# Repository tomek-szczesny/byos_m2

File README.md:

# byos_m2
Build Your Own System - a collection of stackable add-ons

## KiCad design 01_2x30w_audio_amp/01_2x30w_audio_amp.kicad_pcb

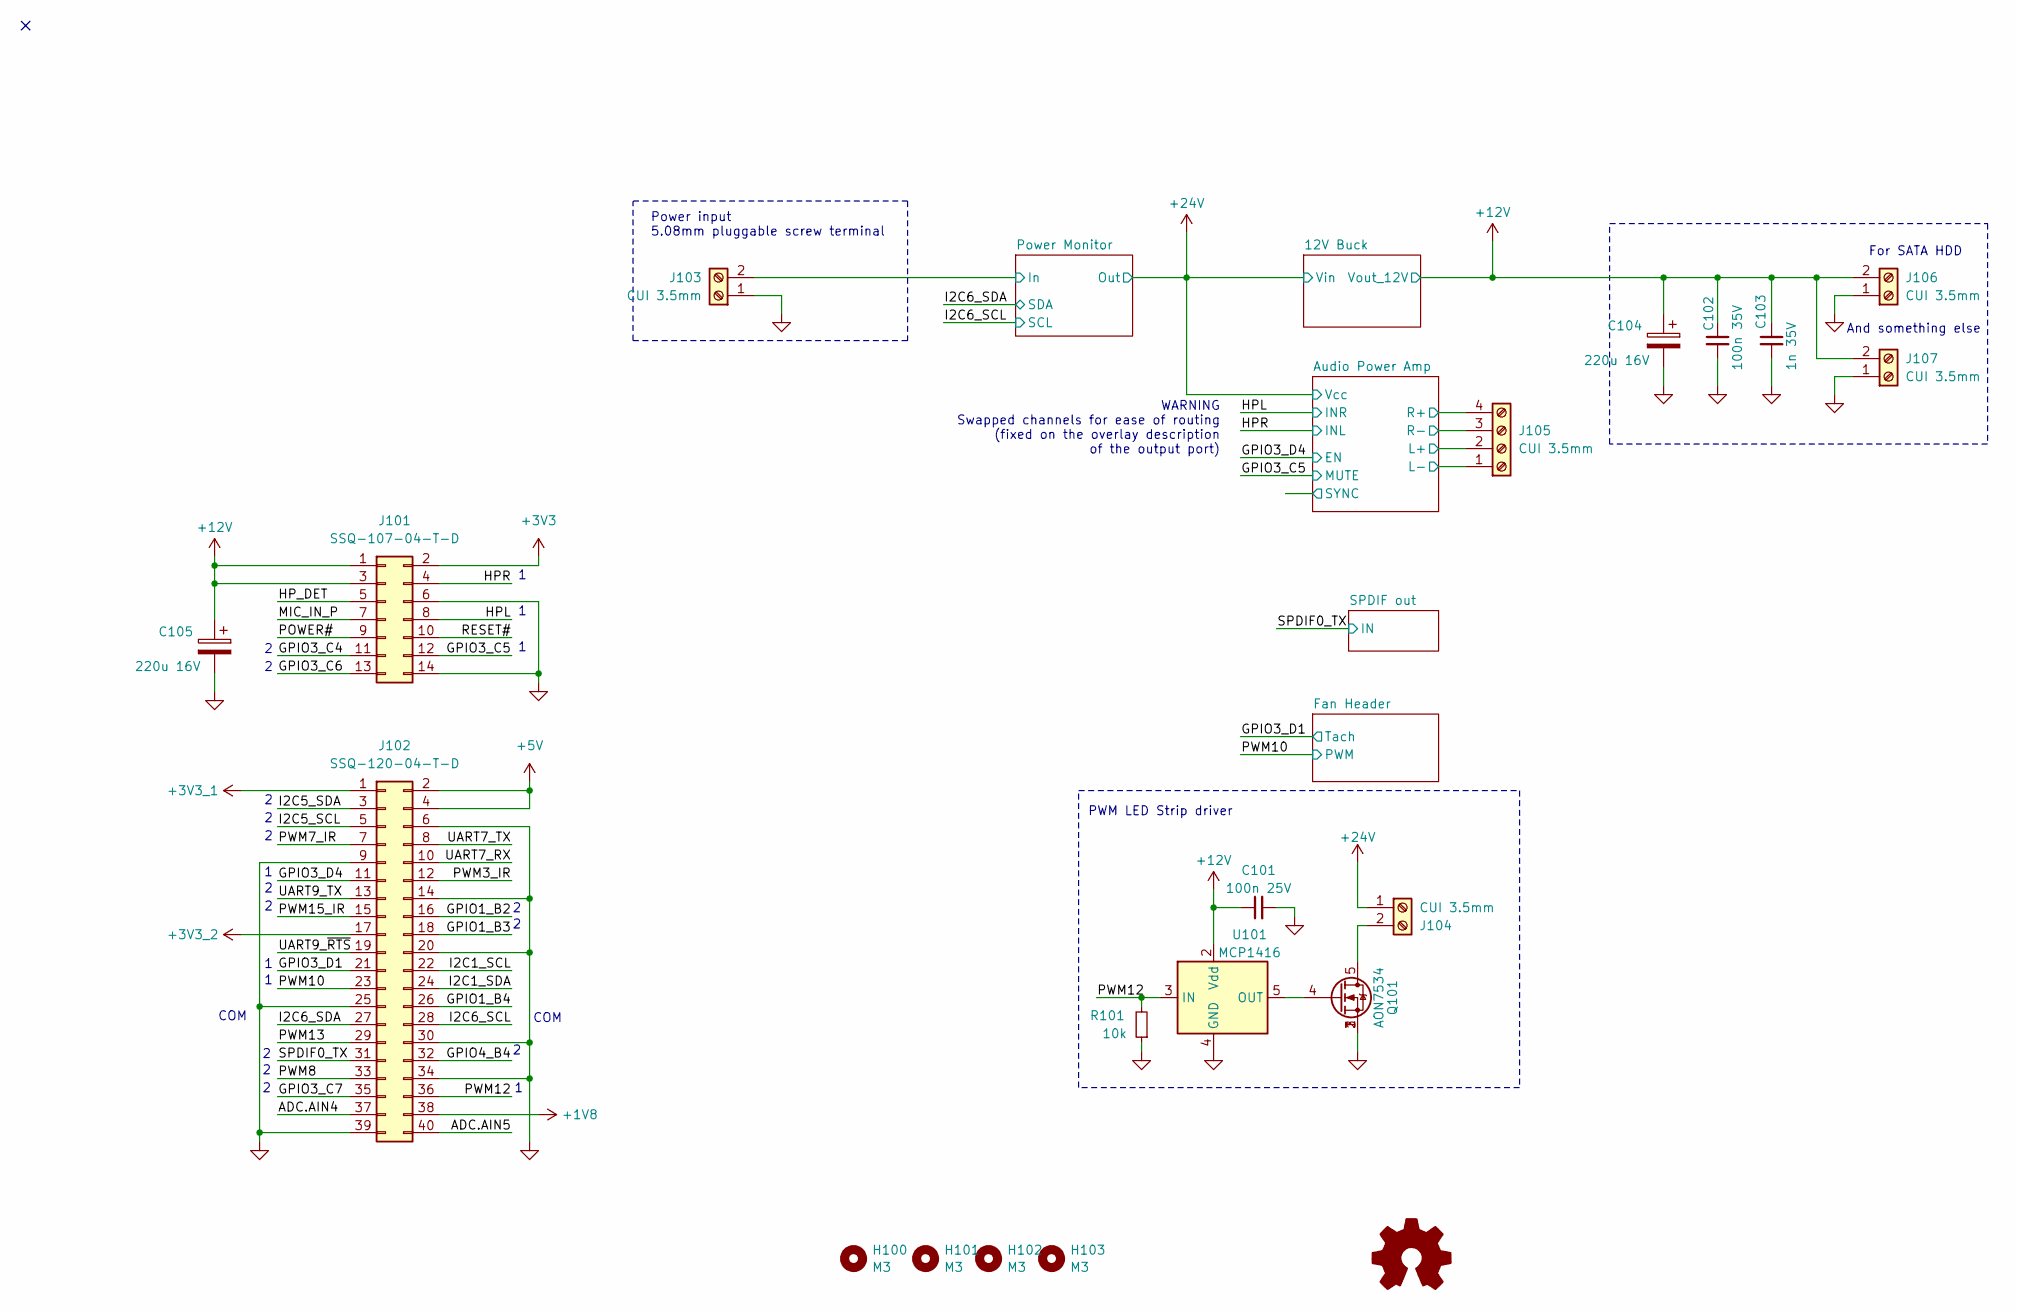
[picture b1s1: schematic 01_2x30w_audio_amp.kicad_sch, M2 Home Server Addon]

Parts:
C101: 100n 25V; C_0603_1608Metric
C102: 100n 35V; C_0603_1608Metric
C103: 1n 35V; C_0603_1608Metric
C104, C105: A750EK227M1CAAE016; CP_Radial_D6.3mm_P2.50mm
H100, H101, H102, H103: M3; MountingHole_3.2mm_M3_DIN965_Pad_TopBottom
J101: SSQ-107-04-T-D; PinSocket_2x07_P2.54mm_Vertical
J102: SSQ-120-04-T-D; PinSocket_2x20_P2.54mm_Vertical
J103, J104, J106, J107: CUI 3.5mm; CUI_TBP03R1-350-02BE
J105: CUI 3.5mm; CUI_TBP03R1-350-04BE
Q101: AON7534; AO_DFN3x3mm
R101: 10k; R_0603_1608Metric
SYM101: Logo_Open_Hardware_Small; OSHW-Logo_11.4x12mm_SilkScreen
U101: MCP1416; SOT-23-5

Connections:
+1V8: J102.38
+3V3: J101.2
+3V3_1: J102.1; also elsewhere on the board
+3V3_2: J102.17; also elsewhere on the board
+5V: J102.2, J102.4
+12V: C101.1, C102.1, C103.1, C104.1, C105.1, J101.1, J101.3, J106.2, J107.2, U101.2 (Vdd); also elsewhere on the board
+24V: J104.1; also elsewhere on the board
/ADC.AIN4: J102.37
/ADC.AIN5: J102.40
/Audio Power Amp/L+: J105.2; also elsewhere on the board
/Audio Power Amp/L-: J105.1; also elsewhere on the board
/Audio Power Amp/R+: J105.4; also elsewhere on the board
/Audio Power Amp/R-: J105.3; also elsewhere on the board
/GPIO1_B2: J102.16
/GPIO1_B3: J102.18
/GPIO1_B4: J102.26
/GPIO3_C4: J101.11
/GPIO3_C5: J101.12; also elsewhere on the board
/GPIO3_C6: J101.13
/GPIO3_C7: J102.35
/GPIO3_D1: J102.21; also elsewhere on the board
/GPIO3_D4: J102.11; also elsewhere on the board
/GPIO4_B4: J102.32
/HPL: J101.8; also elsewhere on the board
/HPR: J101.4; also elsewhere on the board
/HP_DET: J101.5
/I2C1_SCL: J102.22
/I2C1_SDA: J102.24
/I2C5_SCL: J102.5
/I2C5_SDA: J102.3
/I2C6_SCL: J102.28; also elsewhere on the board
/I2C6_SDA: J102.27; also elsewhere on the board
/MIC_IN_P: J101.7
/POWER#: J101.9
/PWM3_IR: J102.12
/PWM7_IR: J102.7
/PWM8: J102.33
/PWM10: J102.23; also elsewhere on the board
/PWM12: J102.36, R101.2, U101.3 (IN)
/PWM13: J102.29
/PWM15_IR: J102.15
/Power Monitor/In: J103.2; also elsewhere on the board
/RESET#: J101.10
/SPDIF0_TX: J102.31; also elsewhere on the board
/UART7_RX: J102.10
/UART7_TX: J102.8
/UART9_TX: J102.13
/UART9_~RTS: J102.19
GND: C101.2, C102.2, C103.2, C104.2, C105.2, J101.6, J101.14, J102.6, J102.9, J102.14, J102.20, J102.25, J102.30, J102.34, J102.39, J103.1, J106.1, J107.1, Q101.1 (S), Q101.2 (S), Q101.3 (S), R101.1, U101.4 (GND); also elsewhere on the board
unnamed: J104.2, Q101.5 (D)
unnamed: Q101.4 (G), U101.5 (OUT)

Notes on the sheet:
PWM LED Strip driver
COM
For SATA HDD
Power input 5.08mm pluggable screw terminal
WARNING Swapped channels for ease of routing (fixed on the overlay description of the output port)
And something else

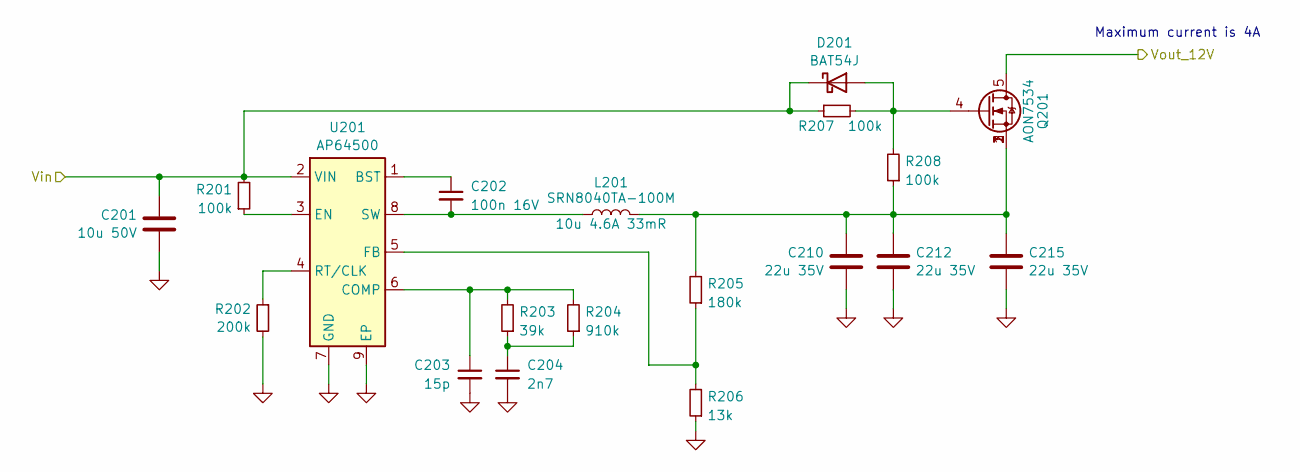
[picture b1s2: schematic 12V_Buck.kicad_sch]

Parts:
C201: 10u 50V; C_1206_3216Metric
C202: 100n 16V; C_0603_1608Metric; LCSC C57112
C203: 15p; C_0603_1608Metric
C204: 2n7; C_0603_1608Metric
C210, C212, C215: 22u 35V; C_1206_3216Metric
D201: BAT54J; D_SOD-323F
L201: SRN8040TA-100M; L_Bourns_SRN8040TA
Q201: AON7534; AO_DFN3x3mm
R201: 100k; R_0603_1608Metric; LCSC C25803
R202: 200k; R_0603_1608Metric; LCSC C23212
R203: 39k; R_0603_1608Metric; LCSC C23212
R204: 910k; R_0603_1608Metric; LCSC C23212
R205: 180k; R_0603_1608Metric; LCSC C4216
R206: 13k; R_0603_1608Metric; LCSC C23234
R207: 100k; R_0603_1608Metric
R208: 100k; R_0603_1608Metric; LCSC C4216
U201: AP64500; SOIC-8-1EP_3.9x4.9mm_P1.27mm_EP2.62x3.51mm

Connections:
+12V: Q201.5 (D); also elsewhere on the board
+24V: C201.1, D201.1 (K), R201.2, R207.1, U201.2 (VIN); also elsewhere on the board
GND: C201.2, C203.2, C204.2, C210.2, C212.2, C215.2, R202.2, R206.1, U201.7 (GND), U201.9 (EP); also elsewhere on the board
unnamed: C204.1, R203.1, R204.1
unnamed: C210.1, C212.1, C215.1, L201.2, Q201.1 (S), Q201.2 (S), Q201.3 (S), R205.2, R208.1
unnamed: D201.2 (A), Q201.4 (G), R207.2, R208.2
unnamed: C202.1, U201.1 (BST)
unnamed: C203.1, R203.2, R204.2, U201.6 (COMP)
unnamed: R201.1, U201.3 (EN)
unnamed: R205.1, R206.2, U201.5 (FB)
unnamed: R202.1, U201.4 (RT/CLK)
unnamed: C202.2, L201.1, U201.8 (SW)

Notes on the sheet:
Maximum current is 4A

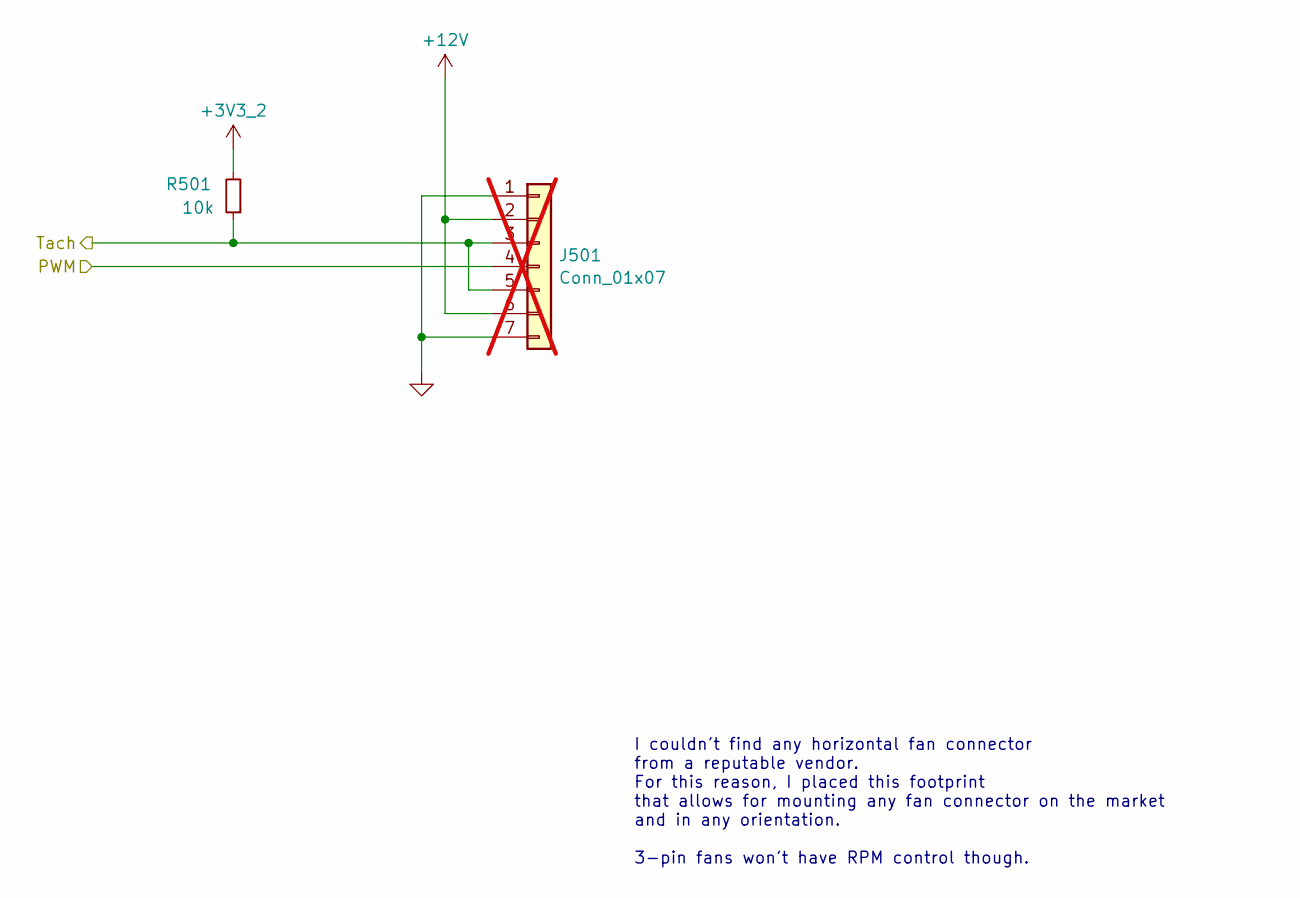
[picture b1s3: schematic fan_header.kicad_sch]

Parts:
J501: Conn_01x07; PinSocket_1x07_P2.54mm_Vertical; not fitted
R501: 10k; R_0603_1608Metric

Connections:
+3V3_2: R501.2; also elsewhere on the board
+12V: J501.2, J501.6; also elsewhere on the board
/GPIO3_D1: J501.3, J501.5, R501.1; also elsewhere on the board
/PWM10: J501.4; also elsewhere on the board
GND: J501.1, J501.7; also elsewhere on the board

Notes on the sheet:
I couldn't find any horizontal fan connector from a reputable vendor. For this reason, I placed this footprint that allows for mounting any fan connector on the market and in any orientation. 3-pin fans won't have RPM control though.

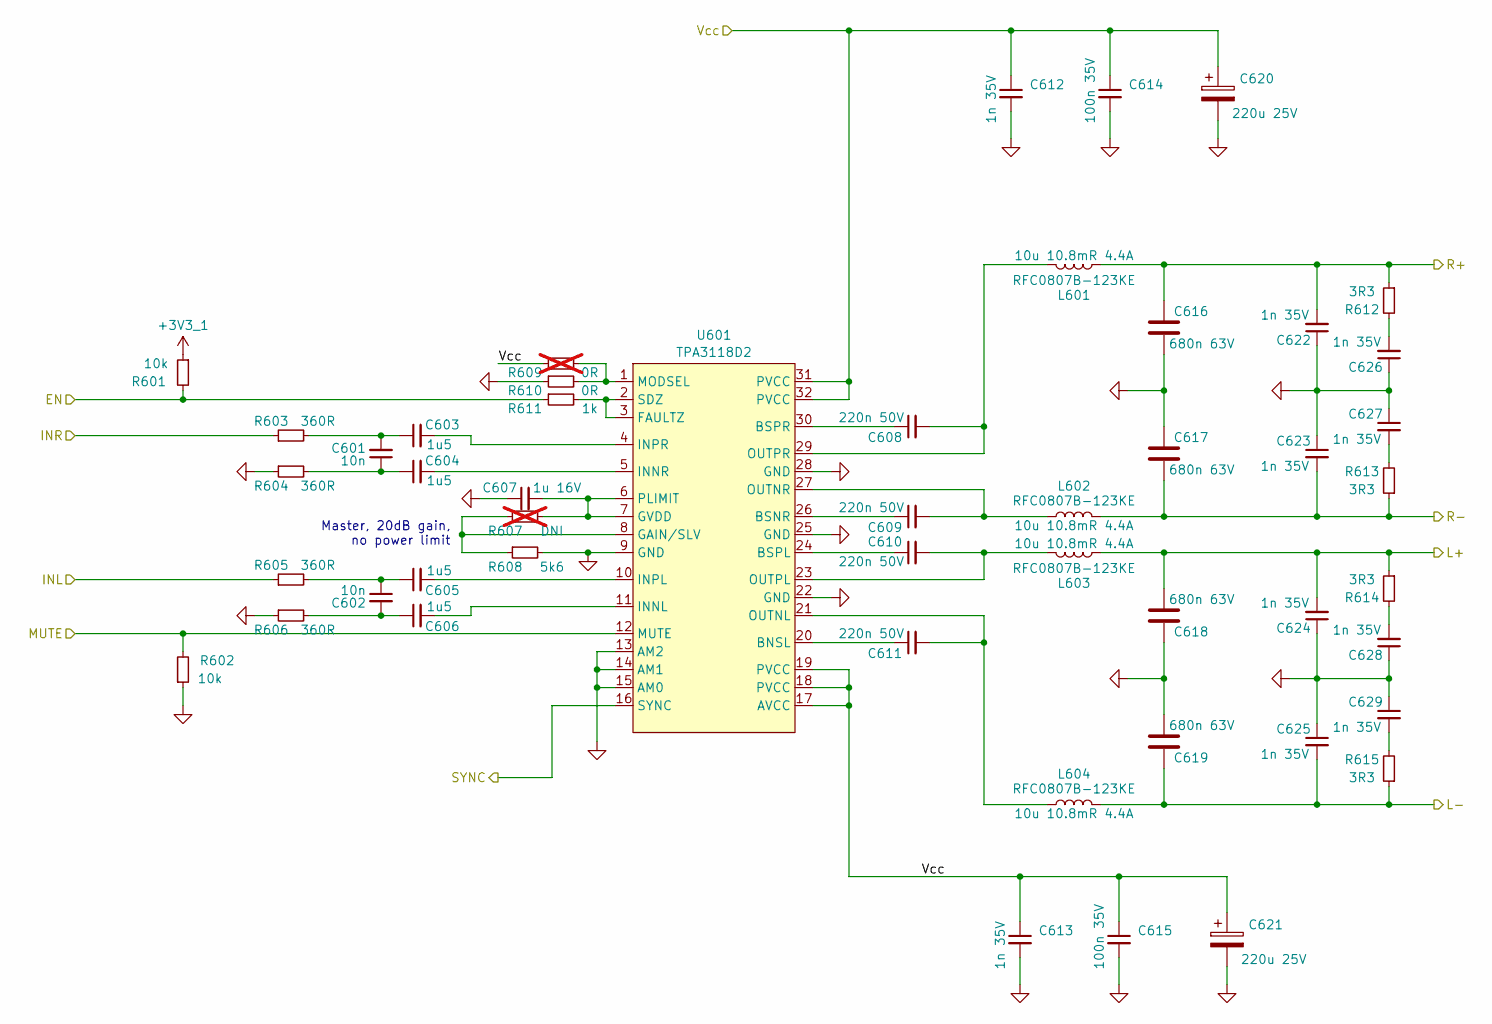
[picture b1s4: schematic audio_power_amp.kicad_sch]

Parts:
C601, C602: 10n; C_0603_1608Metric
C603, C604, C605, C606: 1u5; C_0603_1608Metric
C607: 1u 16V; C_0603_1608Metric
C608, C609, C610, C611: 220n 50V; C_0603_1608Metric
C612, C613, C622, C623, C624, C625, C626, C627, C628, C629: 1n 35V; C_0603_1608Metric
C614, C615: 100n 35V; C_0603_1608Metric
C616, C617, C618, C619: B32529C684J; C_Rect_L7.2mm_W2.5mm_P5.00mm_FKS2_FKP2_MKS2_MKP2
C620, C621: A750KS227M1EAAE015; CP_Radial_D8.0mm_P3.50mm
L601, L602, L603, L604: RFC0807B-123KE; SER1360182KLD
R601, R602: 10k; R_0603_1608Metric
R603, R604, R605, R606: 360R; R_0603_1608Metric
R607: DNI; R_0603_1608Metric; not fitted
R608: 5k6; R_0603_1608Metric
R609: 0R; R_0603_1608Metric; not fitted
R610: 0R; R_0603_1608Metric
R611: 1k; R_0603_1608Metric
R612, R613, R614, R615: 3R3; R_0603_1608Metric
U601: TPA3118D2; HTSSOP-32-1EP_6.1x11mm_P0.65mm_EP5.2x11mm_Mask4.11x4.36mm_T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

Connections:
+3V3_1: R601.1; also elsewhere on the board
+24V: C612.1, C613.1, C614.1, C615.1, C620.1, C621.1, R609.1, U601.17 (AVCC), U601.18 (PVCC), U601.19 (PVCC), U601.31 (PVCC), U601.32 (PVCC); also elsewhere on the board
/Audio Power Amp/L+: C618.1, C624.2, L603.1, R614.1; also elsewhere on the board
/Audio Power Amp/L-: C619.2, C625.2, L604.1, R615.1; also elsewhere on the board
/Audio Power Amp/R+: C616.2, C622.2, L601.2, R612.1; also elsewhere on the board
/Audio Power Amp/R-: C617.1, C623.2, L602.2, R613.1; also elsewhere on the board
/Audio Power Amp/SYNC: U601.16 (SYNC)
/GPIO3_C5: R602.2, U601.12 (MUTE); also elsewhere on the board
/GPIO3_D4: R601.2, R611.1; also elsewhere on the board
/HPL: R603.1; also elsewhere on the board
/HPR: R605.1; also elsewhere on the board
GND: C607.1, C612.2, C613.2, C614.2, C615.2, C616.1, C617.2, C618.2, C619.1, C620.2, C621.2, C622.1, C623.1, C624.1, C625.1, C626.1, C627.1, C628.1, C629.1, R602.1, R604.1, R606.1, R608.2, R610.1, U601.9 (GND), U601.13 (AM2), U601.14 (AM1), U601.15 (AM0), U601.22 (GND), U601.25 (GND), U601.28 (GND), U601.33 (PAD); also elsewhere on the board
unnamed: C601.1, C604.1, R604.2
unnamed: C601.2, C603.1, R603.2
unnamed: C602.1, C605.1, R605.2
unnamed: C602.2, C606.1, R606.2
unnamed: C626.2, R612.2
unnamed: C627.2, R613.2
unnamed: C628.2, R614.2
unnamed: C629.2, R615.2
unnamed: C611.1, U601.20 (BNSL)
unnamed: C609.1, U601.26 (BSNR)
unnamed: C610.1, U601.24 (BSPL)
unnamed: C608.1, U601.30 (BSPR)
unnamed: R611.2, U601.2 (SDZ), U601.3 (FAULTZ)
unnamed: R607.1, R608.1, U601.8 (GAIN/SLV)
unnamed: C607.2, R607.2, U601.6 (PLIMIT), U601.7 (GVDD)
unnamed: C606.2, U601.11 (INNL)
unnamed: C604.2, U601.5 (INNR)
unnamed: C605.2, U601.10 (INPL)
unnamed: C603.2, U601.4 (INPR)
unnamed: R609.2, R610.2, U601.1 (MODSEL)
unnamed: C611.2, L604.2, U601.21 (OUTNL)
unnamed: C609.2, L602.1, U601.27 (OUTNR)
unnamed: C610.2, L603.2, U601.23 (OUTPL)
unnamed: C608.2, L601.1, U601.29 (OUTPR)

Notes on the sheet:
Master, 20dB gain, no power limit

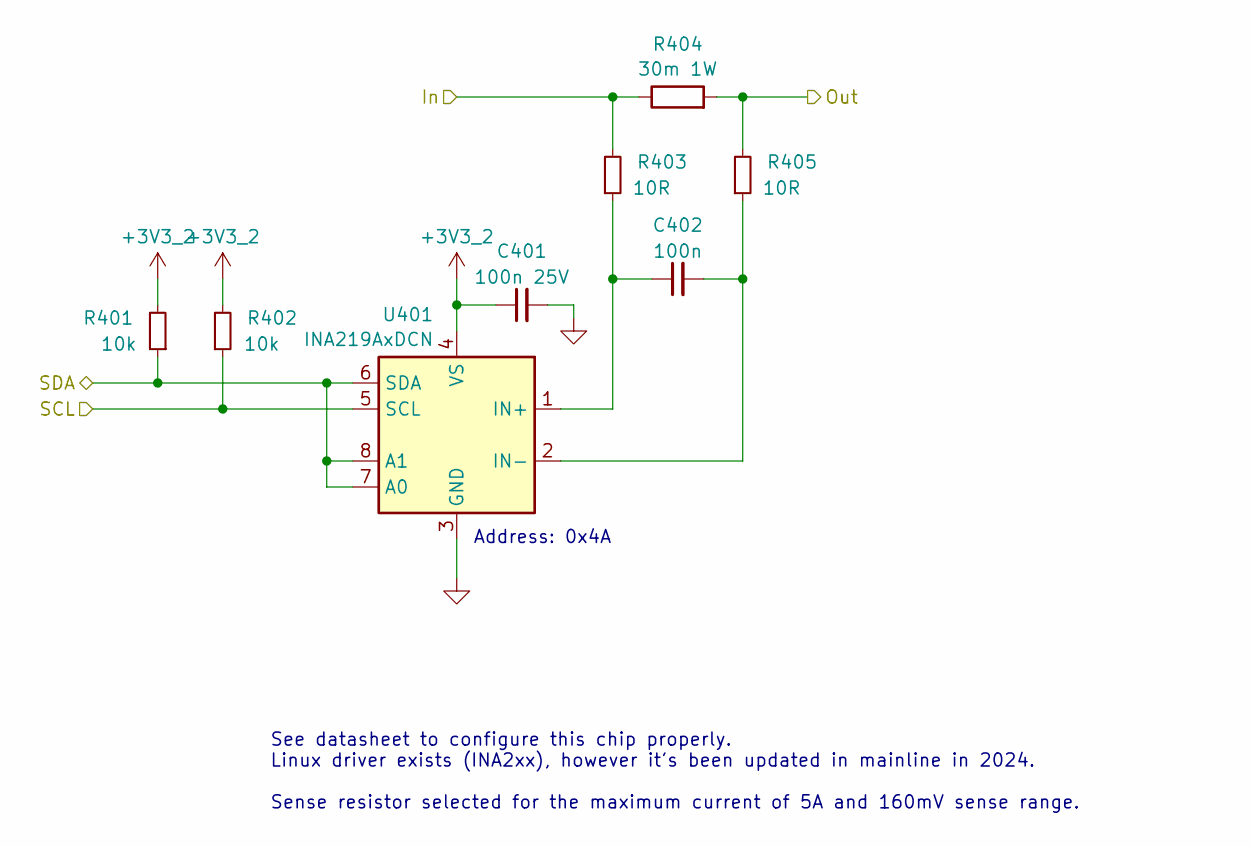
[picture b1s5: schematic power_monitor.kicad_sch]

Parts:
C401: 100n 25V; C_0603_1608Metric
C402: 100n; C_0603_1608Metric
R401, R402: 10k; R_0603_1608Metric
R403, R405: 10R; R_0603_1608Metric
R404: 30m 1W; R_1206_3216Metric
U401: INA219AxDCN; SOT-23-8

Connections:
+3V3_2: C401.1, R401.2, R402.2, U401.4 (VS); also elsewhere on the board
+24V: R404.2, R405.2; also elsewhere on the board
/I2C6_SCL: R402.1, U401.5 (SCL); also elsewhere on the board
/I2C6_SDA: R401.1, U401.6 (SDA), U401.7 (A0), U401.8 (A1); also elsewhere on the board
/Power Monitor/In: R403.2, R404.1; also elsewhere on the board
GND: C401.2, U401.3 (GND); also elsewhere on the board
unnamed: C402.1, R403.1, U401.1 (IN+)
unnamed: C402.2, R405.1, U401.2 (IN-)

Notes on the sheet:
See datasheet to configure this chip properly. Linux driver exists (INA2xx), however it's been updated in mainline in 2024. Sense resistor selected for the maximum current of 5A and 160mV sense range.
Address: 0x4A

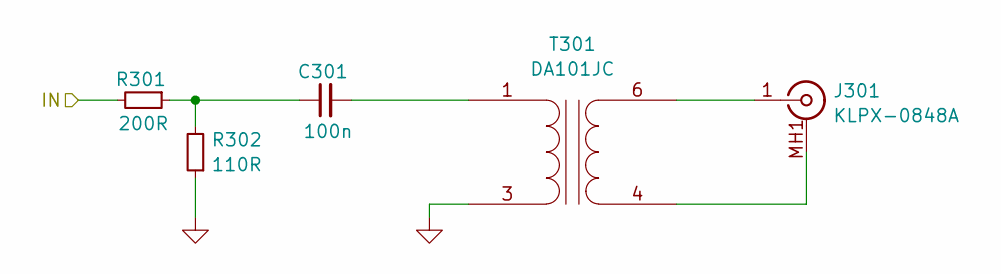
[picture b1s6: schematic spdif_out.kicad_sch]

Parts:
C301: 100n; C_0603_1608Metric
J301: KLPX-0848A; 936
R301: 200R; R_0603_1608Metric
R302: 110R; R_0603_1608Metric
T301: DA101JC; SOP254P1270X635-6N

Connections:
/SPDIF0_TX: R301.2; also elsewhere on the board
GND: R302.1, T301.3 (AB); also elsewhere on the board
unnamed: C301.1, R301.1, R302.2
unnamed: J301.1 (In), T301.6 (SB)
unnamed: C301.2, T301.1 (AA)
unnamed: J301.MH1 (Ext), J301.MH2 (Ext), J301.MH3 (Ext), T301.4 (SA)

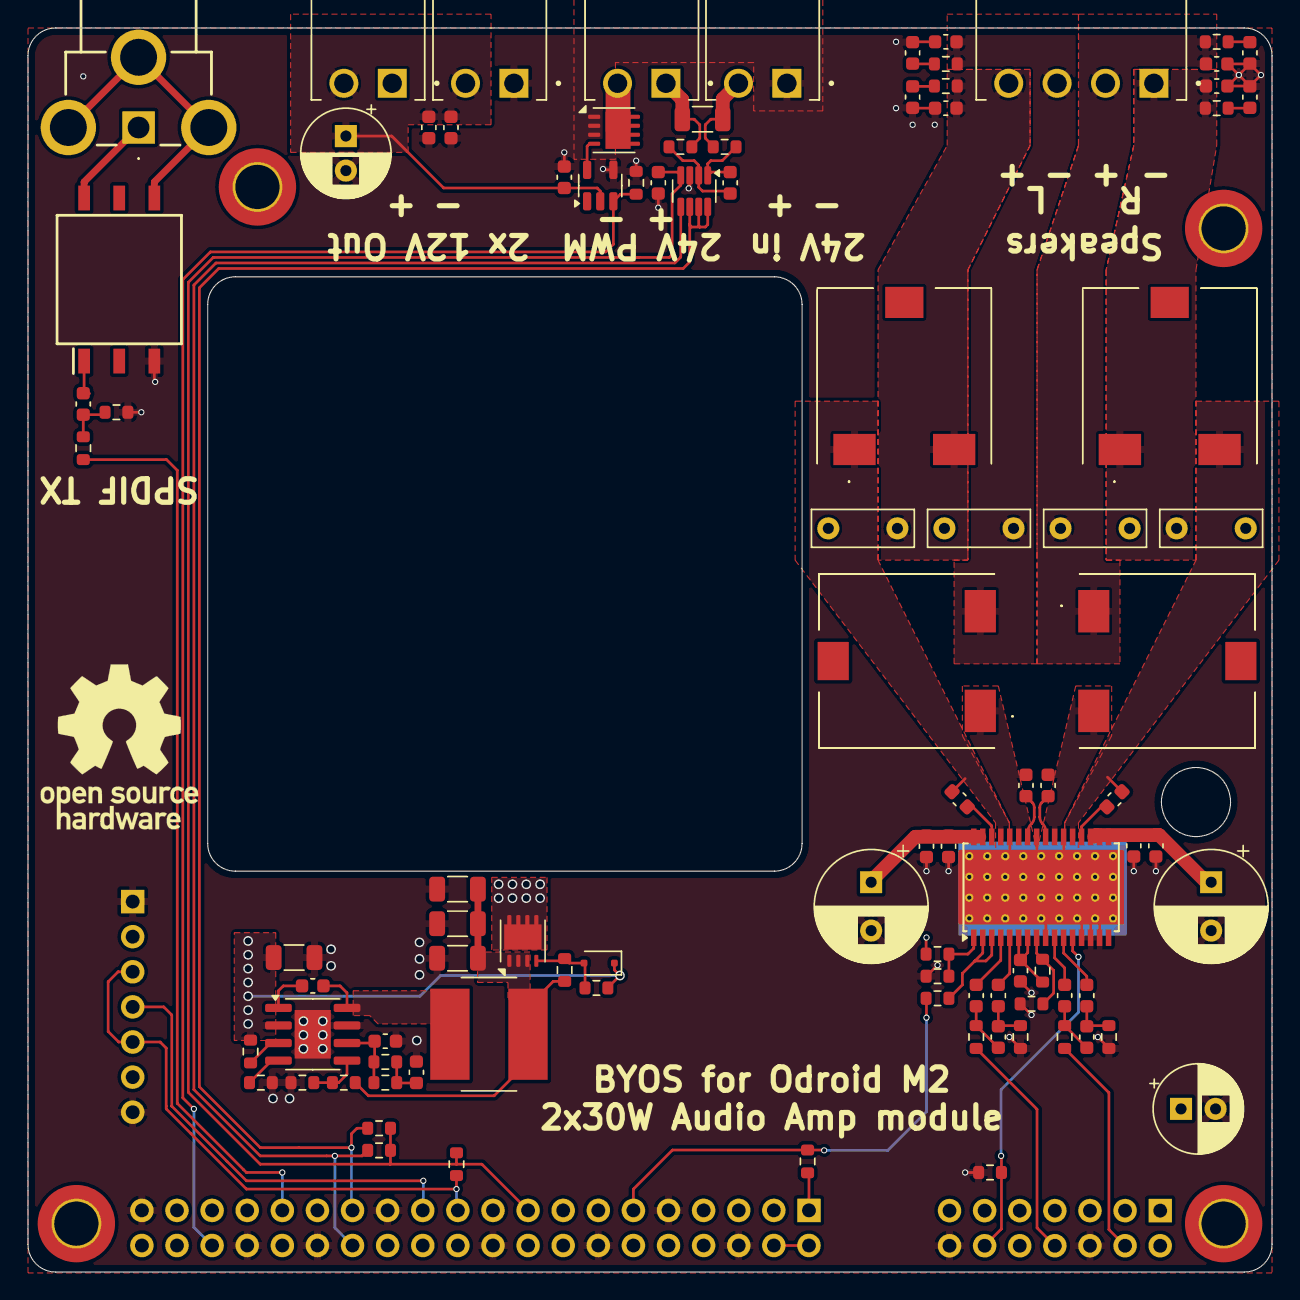
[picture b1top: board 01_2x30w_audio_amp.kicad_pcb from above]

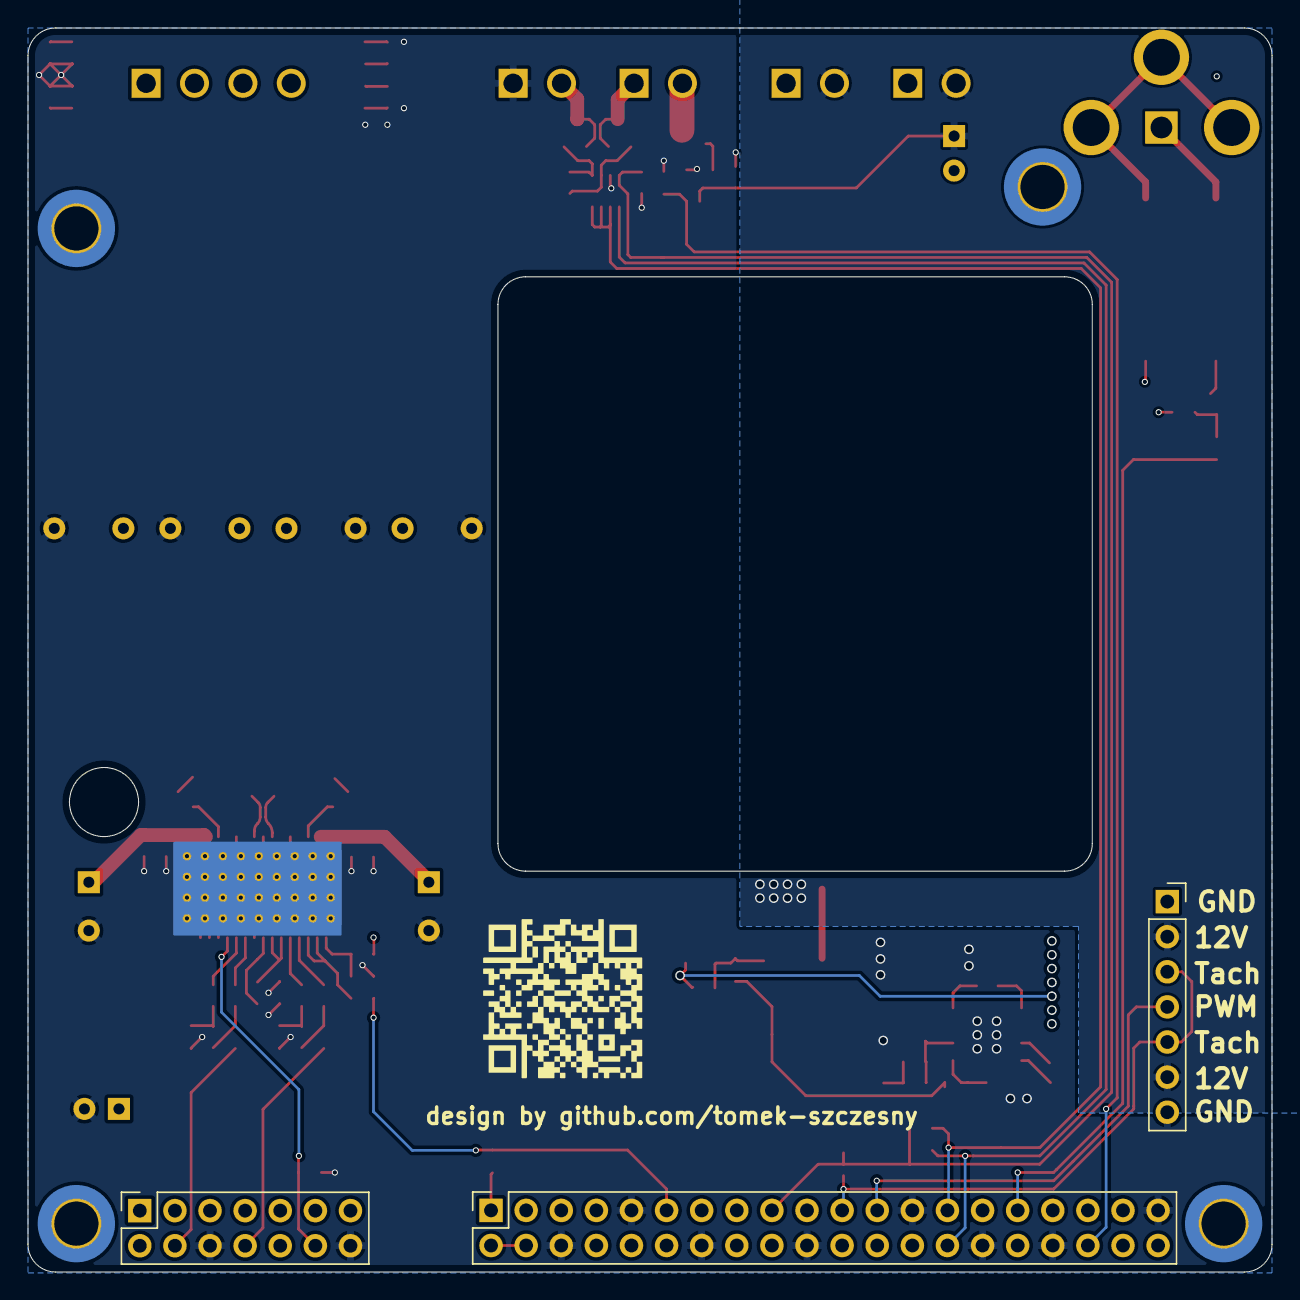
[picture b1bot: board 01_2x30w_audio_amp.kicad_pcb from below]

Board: 4 copper layers, 90.0 x 90.0 mm, 103 parts (3 on the bottom side), 62 nets.

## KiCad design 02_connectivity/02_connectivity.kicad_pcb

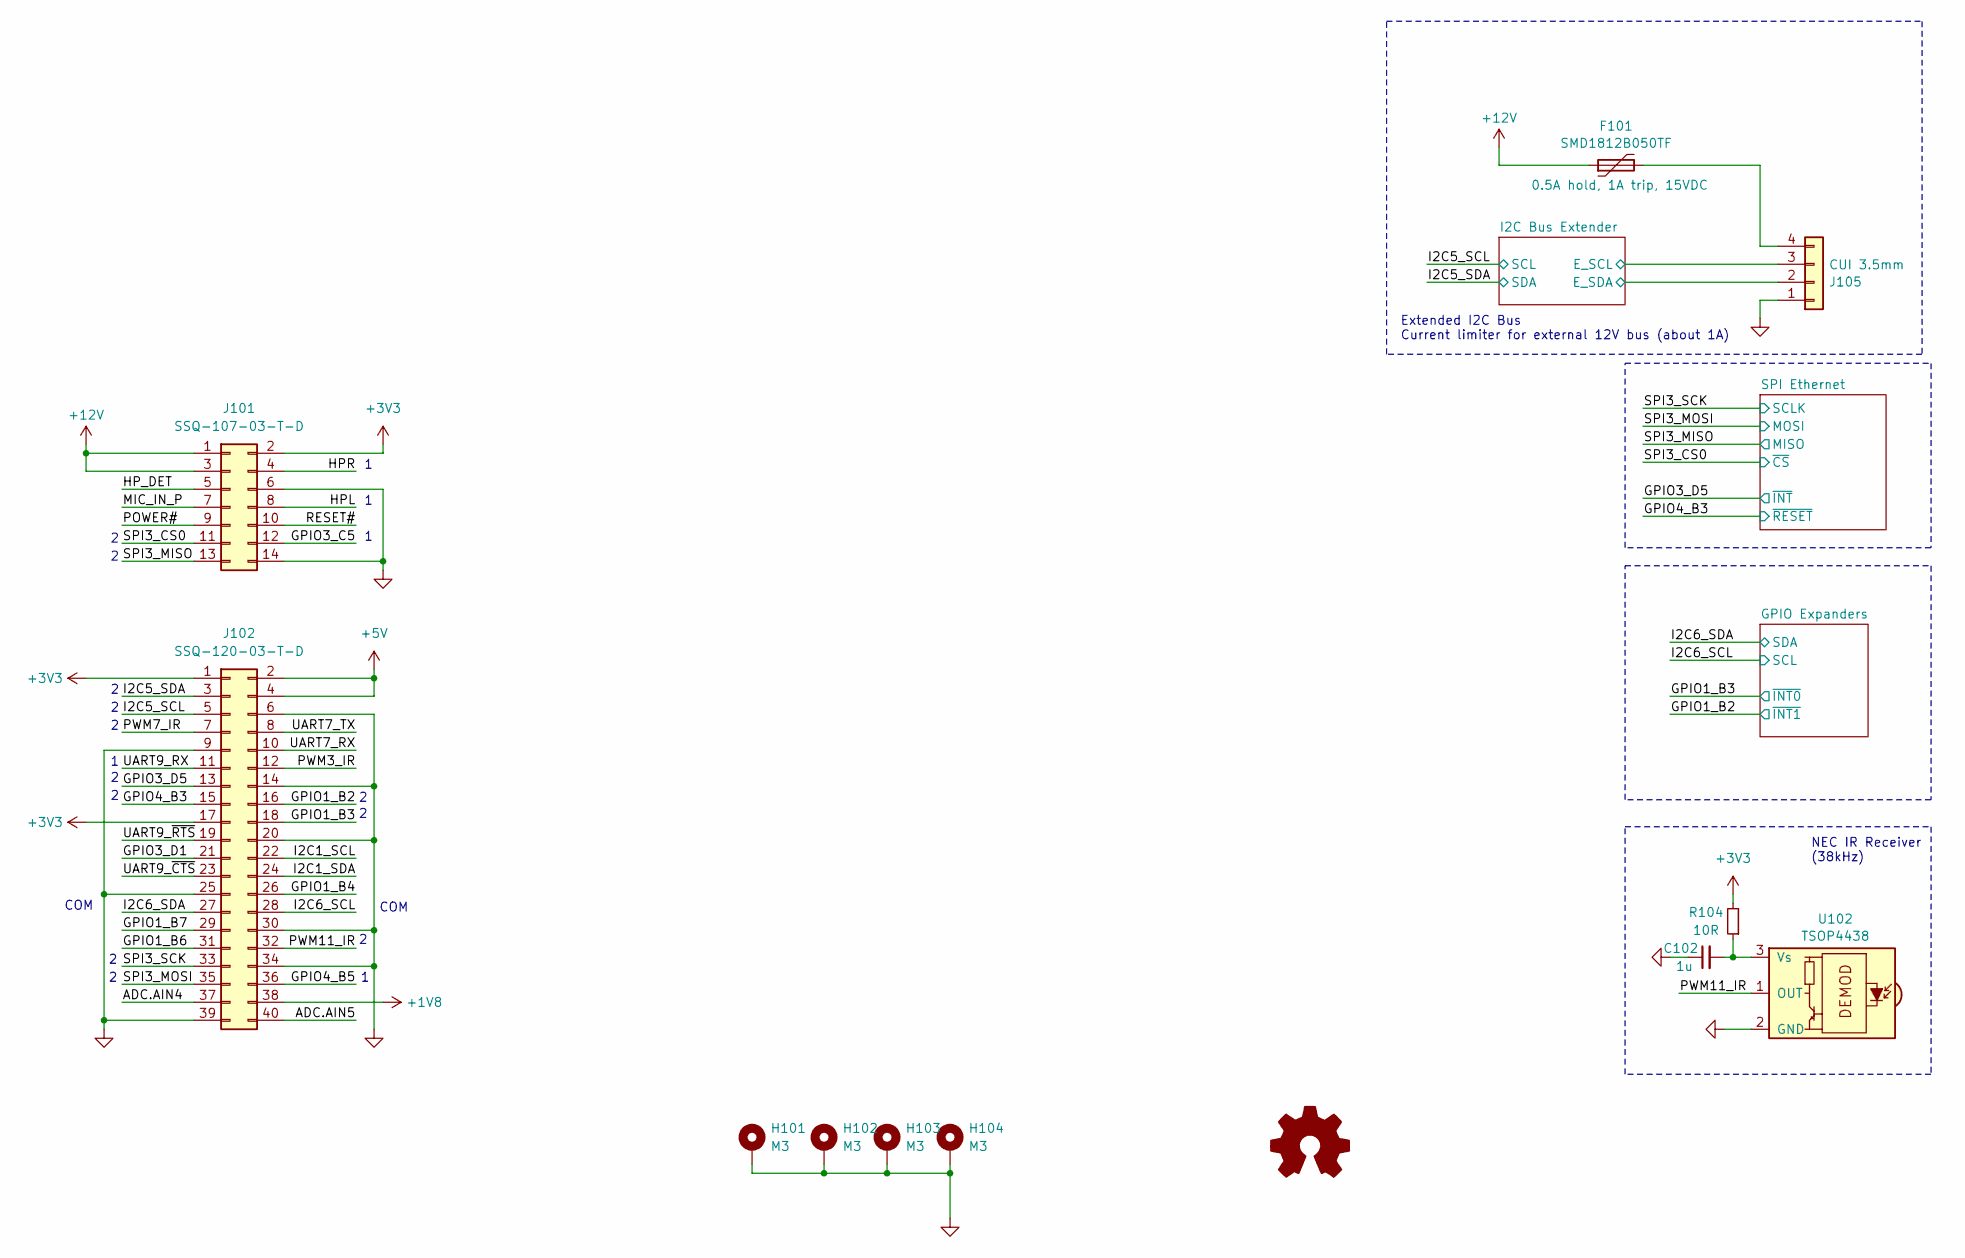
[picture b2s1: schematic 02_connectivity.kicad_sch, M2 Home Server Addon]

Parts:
C102: 1u; C_0603_1608Metric
F101: SMD1812B050TF; Fuse_1812_4532Metric
H101, H102, H103, H104: M3; MountingHole_3.2mm_M3_DIN965_Pad
J101: SSQ-107-03-T-D; PinSocket_2x07_P2.54mm_Vertical
J102: SSQ-120-03-T-D; PinSocket_2x20_P2.54mm_Vertical
J105: CUI 3.5mm; CUI_TBP03R1-350-04BE
R104: 10R; R_0603_1608Metric
SYM101: Logo_Open_Hardware_Small; OSHW-Logo_11.4x12mm_SilkScreen
U102: TSOP4438; Vishay_MOLD-3Pin

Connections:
+1V8: J102.38
+3V3: J101.2, J102.1, J102.17, R104.2; also elsewhere on the board
+5V: J102.2, J102.4; also elsewhere on the board
+12V: F101.1, J101.1, J101.3
/ADC.AIN4: J102.37
/ADC.AIN5: J102.40
/GPIO1_B2: J102.16; also elsewhere on the board
/GPIO1_B3: J102.18; also elsewhere on the board
/GPIO1_B4: J102.26
/GPIO1_B6: J102.31
/GPIO1_B7: J102.29
/GPIO3_C5: J101.12
/GPIO3_D1: J102.21
/GPIO3_D5: J102.13; also elsewhere on the board
/GPIO4_B3: J102.15; also elsewhere on the board
/GPIO4_B5: J102.36
/HPL: J101.8
/HPR: J101.4
/HP_DET: J101.5
/I2C1_SCL: J102.22
/I2C1_SDA: J102.24
/I2C5_SCL: J102.5; also elsewhere on the board
/I2C5_SDA: J102.3; also elsewhere on the board
/I2C6_SCL: J102.28; also elsewhere on the board
/I2C6_SDA: J102.27; also elsewhere on the board
/I2C Bus Extender/E_SCL: J105.3; also elsewhere on the board
/I2C Bus Extender/E_SDA: J105.2; also elsewhere on the board
/MIC_IN_P: J101.7
/POWER#: J101.9
/PWM3_IR: J102.12
/PWM7_IR: J102.7
/PWM11_IR: J102.32, U102.1 (OUT)
/RESET#: J101.10
/SPI3_CS0: J101.11; also elsewhere on the board
/SPI3_MISO: J101.13; also elsewhere on the board
/SPI3_MOSI: J102.35; also elsewhere on the board
/SPI3_SCK: J102.33; also elsewhere on the board
/UART7_RX: J102.10
/UART7_TX: J102.8
/UART9_RX: J102.11
/UART9_~CTS: J102.23
/UART9_~RTS: J102.19
GND: C102.1, H101.1, H102.1, H103.1, H104.1, J101.6, J101.14, J102.6, J102.9, J102.14, J102.20, J102.25, J102.30, J102.34, J102.39, J105.1, U102.2 (GND); also elsewhere on the board
unnamed: F101.2, J105.4
unnamed: C102.2, R104.1, U102.3 (Vs)

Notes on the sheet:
COM
NEC IR Receiver (38kHz)
Extended I2C Bus Current limiter for external 12V bus (about 1A)
